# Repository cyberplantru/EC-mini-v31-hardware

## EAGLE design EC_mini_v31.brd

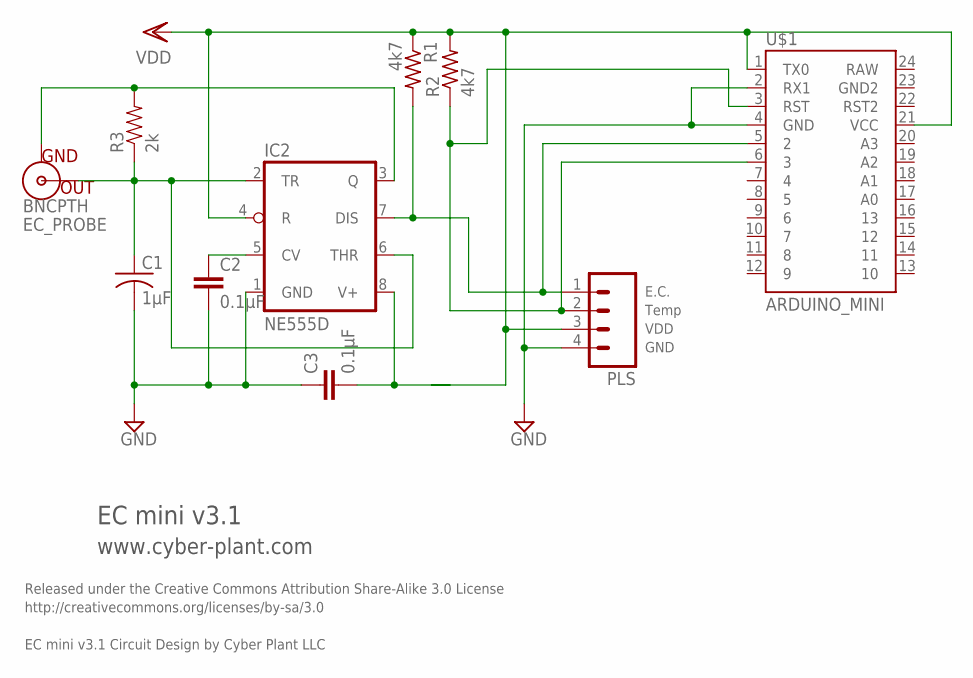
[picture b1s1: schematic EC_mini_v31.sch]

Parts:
C1: 1µF; C050-045X075
C2, C3: 0.1µF; 1206
EC_PROBE: BNCPTH; BNC
IC2: NE555D; SO08
PLS: M04PTH; 1X04
R1, R2: 4k7; 0207/10
R3: 2k; 1206
U$1: ARDUINO_MINI

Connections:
GND: C1.2, C2.2, C3.1, IC2.1 (GND), PLS.4, U$1.2 (RX1), U$1.4 (GND)
unnamed: PLS.2, R2.1, U$1.3 (RST), U$1.6 (3)
unnamed: IC2.7 (DIS), PLS.1, R1.2, U$1.5 (2)
unnamed: C1.1, EC_PROBE.S (OUT), IC2.2 (TR), IC2.6 (THR), R3.1
unnamed: EC_PROBE.GND, IC2.3 (Q), R3.2
unnamed: C2.1, IC2.5 (CV)
VDD: C3.2, IC2.4 (R), IC2.8 (V+), PLS.3, R1.1, R2.2, U$1.1 (TX0), U$1.21 (VCC)

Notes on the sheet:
EC mini v3.1
www.cyber-plant.com
Released under the Creative Commons Attribution Share-Alike 3.0 License
http://creativecommons.org/licenses/by-sa/3.0
EC mini v3.1 Circuit Design by Cyber Plant LLC
GND
VDD
Temp
E.C.

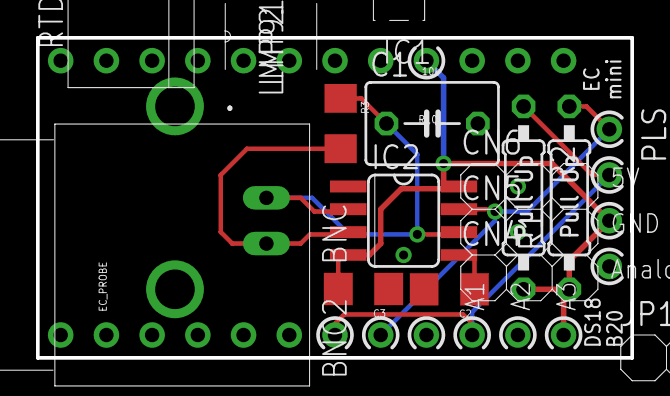
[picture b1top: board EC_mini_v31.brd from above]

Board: 2 copper layers, 33.0 x 17.8 mm, 10 parts (1 on the bottom side), 7 nets.

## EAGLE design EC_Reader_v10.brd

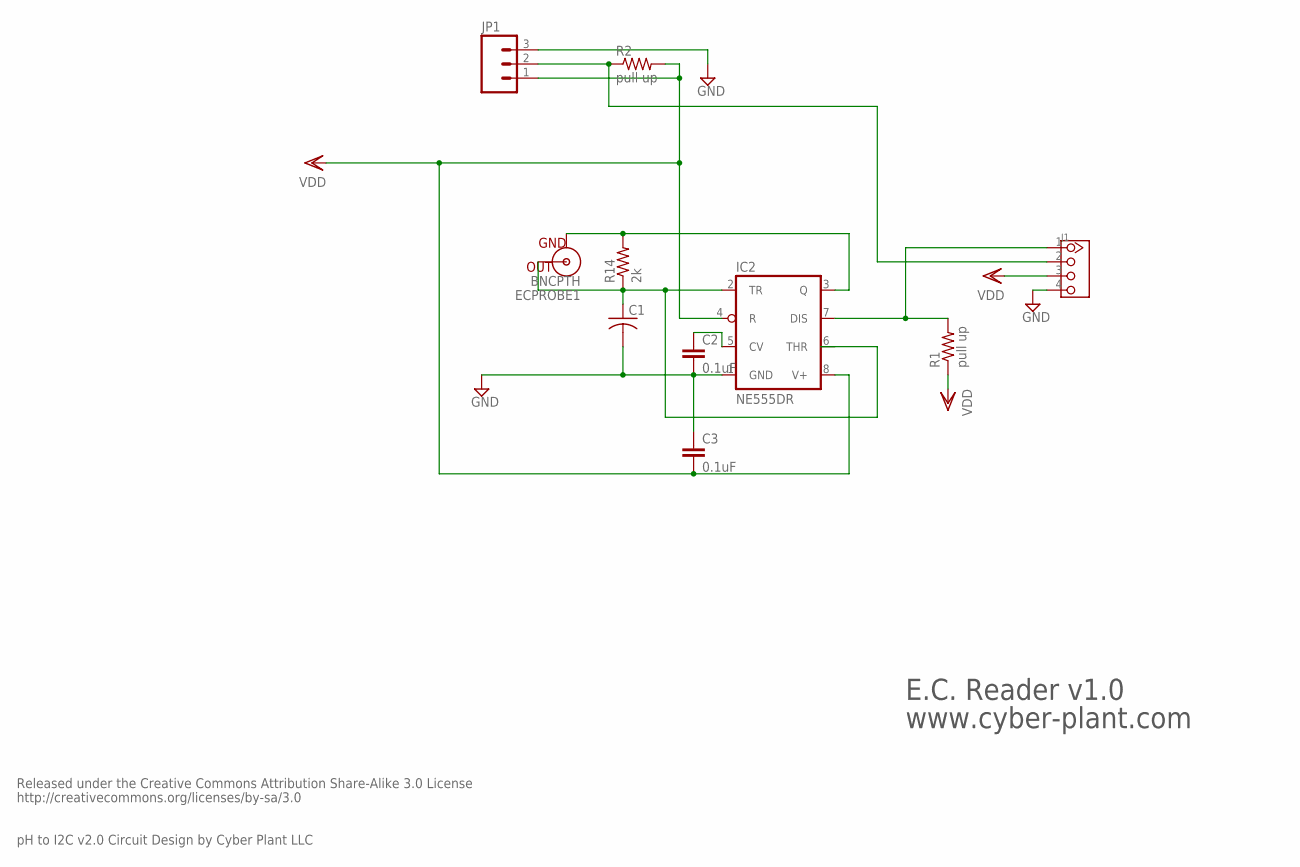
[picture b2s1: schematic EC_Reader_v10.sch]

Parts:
C1: C-US050-045X075; C050-045X075
C2, C3: 0.1uF; 1206
ECPROBE1: BNCPTH; BNC
IC2: NE555DR; SO08
J1: TWIG-4P-2.090D; 4P-2.0-90D
JP1: M03PTH; 1X03
R1, R2: pull up; AXIAL-0.4
R14: 2k; 1206

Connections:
GND: C1.2, C2.2, C3.1, IC2.1 (GND), J1.4, JP1.3
unnamed: J1.2, JP1.2, R2.P$1 (1)
unnamed: IC2.7 (DIS), J1.1, R1.P$2 (2)
unnamed: C1.1, ECPROBE1.S (OUT), IC2.2 (TR), IC2.6 (THR), R14.1
unnamed: ECPROBE1.GND, IC2.3 (Q), R14.2
unnamed: C2.1, IC2.5 (CV)
VDD: C3.2, IC2.4 (R), IC2.8 (V+), J1.3, JP1.1, R1.P$1 (1), R2.P$2 (2)

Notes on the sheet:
E.C. Reader v1.0
www.cyber-plant.com
Released under the Creative Commons Attribution Share-Alike 3.0 License
http://creativecommons.org/licenses/by-sa/3.0
pH to I2C v2.0 Circuit Design by Cyber Plant LLC

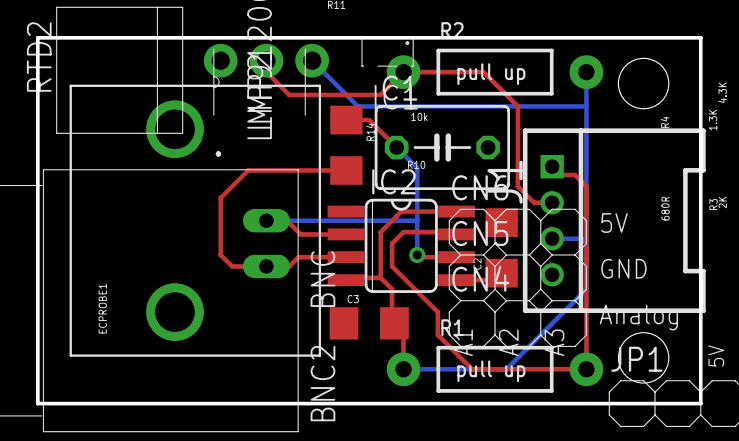
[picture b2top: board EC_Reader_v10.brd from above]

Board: 2 copper layers, 36.8 x 20.3 mm, 10 parts (1 on the bottom side), 7 nets.

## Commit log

2015-12-03 :neckbeard: Added .gitattributes & .gitignore files
2015-12-03 master
2016-02-16 master
    pdf

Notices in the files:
parts and their libraries:
Arduinominimi: Licensing: CC v3.0 Share-Alike You are welcome to use this library for commercial purposes.
